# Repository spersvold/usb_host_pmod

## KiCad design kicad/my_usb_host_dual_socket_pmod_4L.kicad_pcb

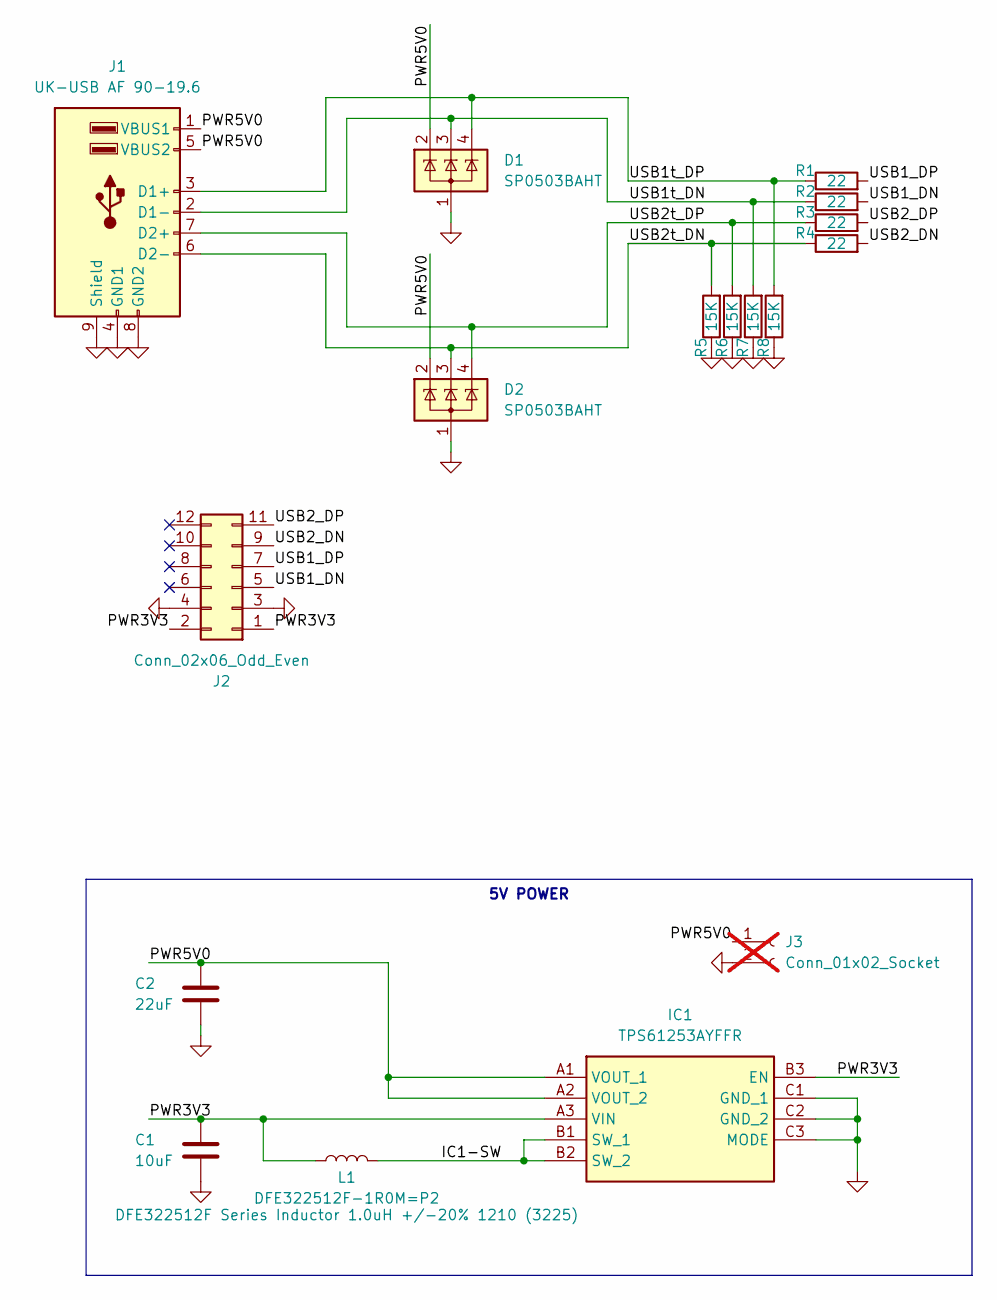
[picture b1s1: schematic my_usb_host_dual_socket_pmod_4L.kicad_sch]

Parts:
C1: 10uF; C_0603_1608Metric
C2: 22uF; C_1206_3216Metric
D1, D2: SP0503BAHT; SOT-143
IC1: TPS61253AYFFR; BGA9C40P3X3_119X129X62; Mouser Part Number 595-TPS61253AYFFR
J1: UK-USB AF 90-19.6; USB_A_Wuerth_61400826021_Horizontal_Stacked
J2: Conn_02x06_Odd_Even; PinHeader_2x06_P2.54mm_Horizontal
J3: Conn_01x02_Socket; PinSocket_1x02_P2.54mm_Vertical; not fitted
L1: DFE322512F-1R0M=P2; L_1210_3225Metric
R1, R2, R3, R4: 22; R_0402_1005Metric
R5, R6, R7, R8: 15K; R_0402_1005Metric

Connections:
/IC1-SW: IC1.B1 (SW_1), IC1.B2 (SW_2), L1.2
/PWR3V3: C1.1, IC1.A3 (VIN), IC1.B3 (EN), J2.1, J2.2, L1.1
/PWR5V0: C2.1, D1.2 (K), D2.2 (K), IC1.A1 (VOUT_1), IC1.A2 (VOUT_2), J1.1 (VBUS1), J1.5 (VBUS2), J3.1
/USB1_DN: J2.5, R2.2
/USB1_DP: J2.7, R1.2
/USB1t_DN: D1.3 (K), J1.2 (D1-), R2.1, R7.2
/USB1t_DP: D1.4 (K), J1.3 (D1+), R1.1, R8.2
/USB2_DN: J2.9, R4.2
/USB2_DP: J2.11, R3.2
/USB2t_DN: D2.3 (K), J1.6 (D2-), R4.1, R5.2
/USB2t_DP: D2.4 (K), J1.7 (D2+), R3.1, R6.2
GND: C1.2, C2.2, D1.1 (A), D2.1 (A), IC1.C1 (GND_1), IC1.C2 (GND_2), IC1.C3 (MODE), J1.4 (GND1), J1.8 (GND2), J1.9 (Shield), J2.3, J2.4, J3.2, R5.1, R6.1, R7.1, R8.1

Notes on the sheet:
5V POWER

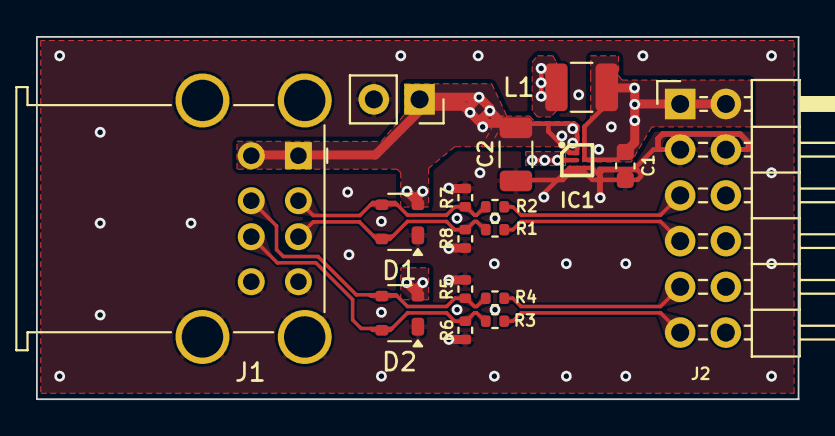
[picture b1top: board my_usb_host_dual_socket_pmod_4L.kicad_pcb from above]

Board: 4 copper layers, 42.3 x 20.1 mm, 17 parts (0 on the bottom side), 12 nets.

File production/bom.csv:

Designator,Footprint,Quantity,Value,LCSC Part #
C1,0402,1,10uF,
"C2, C3",0603,2,10uF,
IC1,BGA9C40P3X3_119X129X62,1,TPS61253AYFFR,
J1,USB_A_Wuerth_61400826021_Horizontal_Stacked,1,UK-USB AF 90-19.6,
J2,PinHeader_2x06_P2.54mm_Horizontal,1,Conn_02x06_Odd_Even,
J3,PinSocket_1x02_P2.54mm_Vertical,1,Conn_01x02_Socket,
L1,1277ASH100MP2,1,DFE322512F-1R0M=P2,
"R1, R2, R3, R4",0402,4,22,
"R5, R6, R7, R8",0402,4,15K,

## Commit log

2024-08-17 Changed 5V0 regulator to TPS61253A which supports more current
2024-08-17 Changed to 4-layer stackup for matched USB 50/90 impedance and added ESD protection
